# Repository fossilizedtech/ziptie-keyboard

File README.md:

# ziptie-keyboard
Everyone has their own preference when it comes to keyboards. This is my attempt to make my dream keyboard. There are a lot of ideas that will be implemented over time and I do not recommend using this as a foundation for any other project unless you don't value your time. I am not an electrical engineer, and I have no idea what I'm doing. I'm just throwing bits and pieces together, hoping that I don't end up burning my house to the ground in the process.

Now that you have been warned, if you want to build this board here is what you will need.

# Bill of Materials
Add materials here

# Building
Step by step instructions on how to get what you need to build and how to build

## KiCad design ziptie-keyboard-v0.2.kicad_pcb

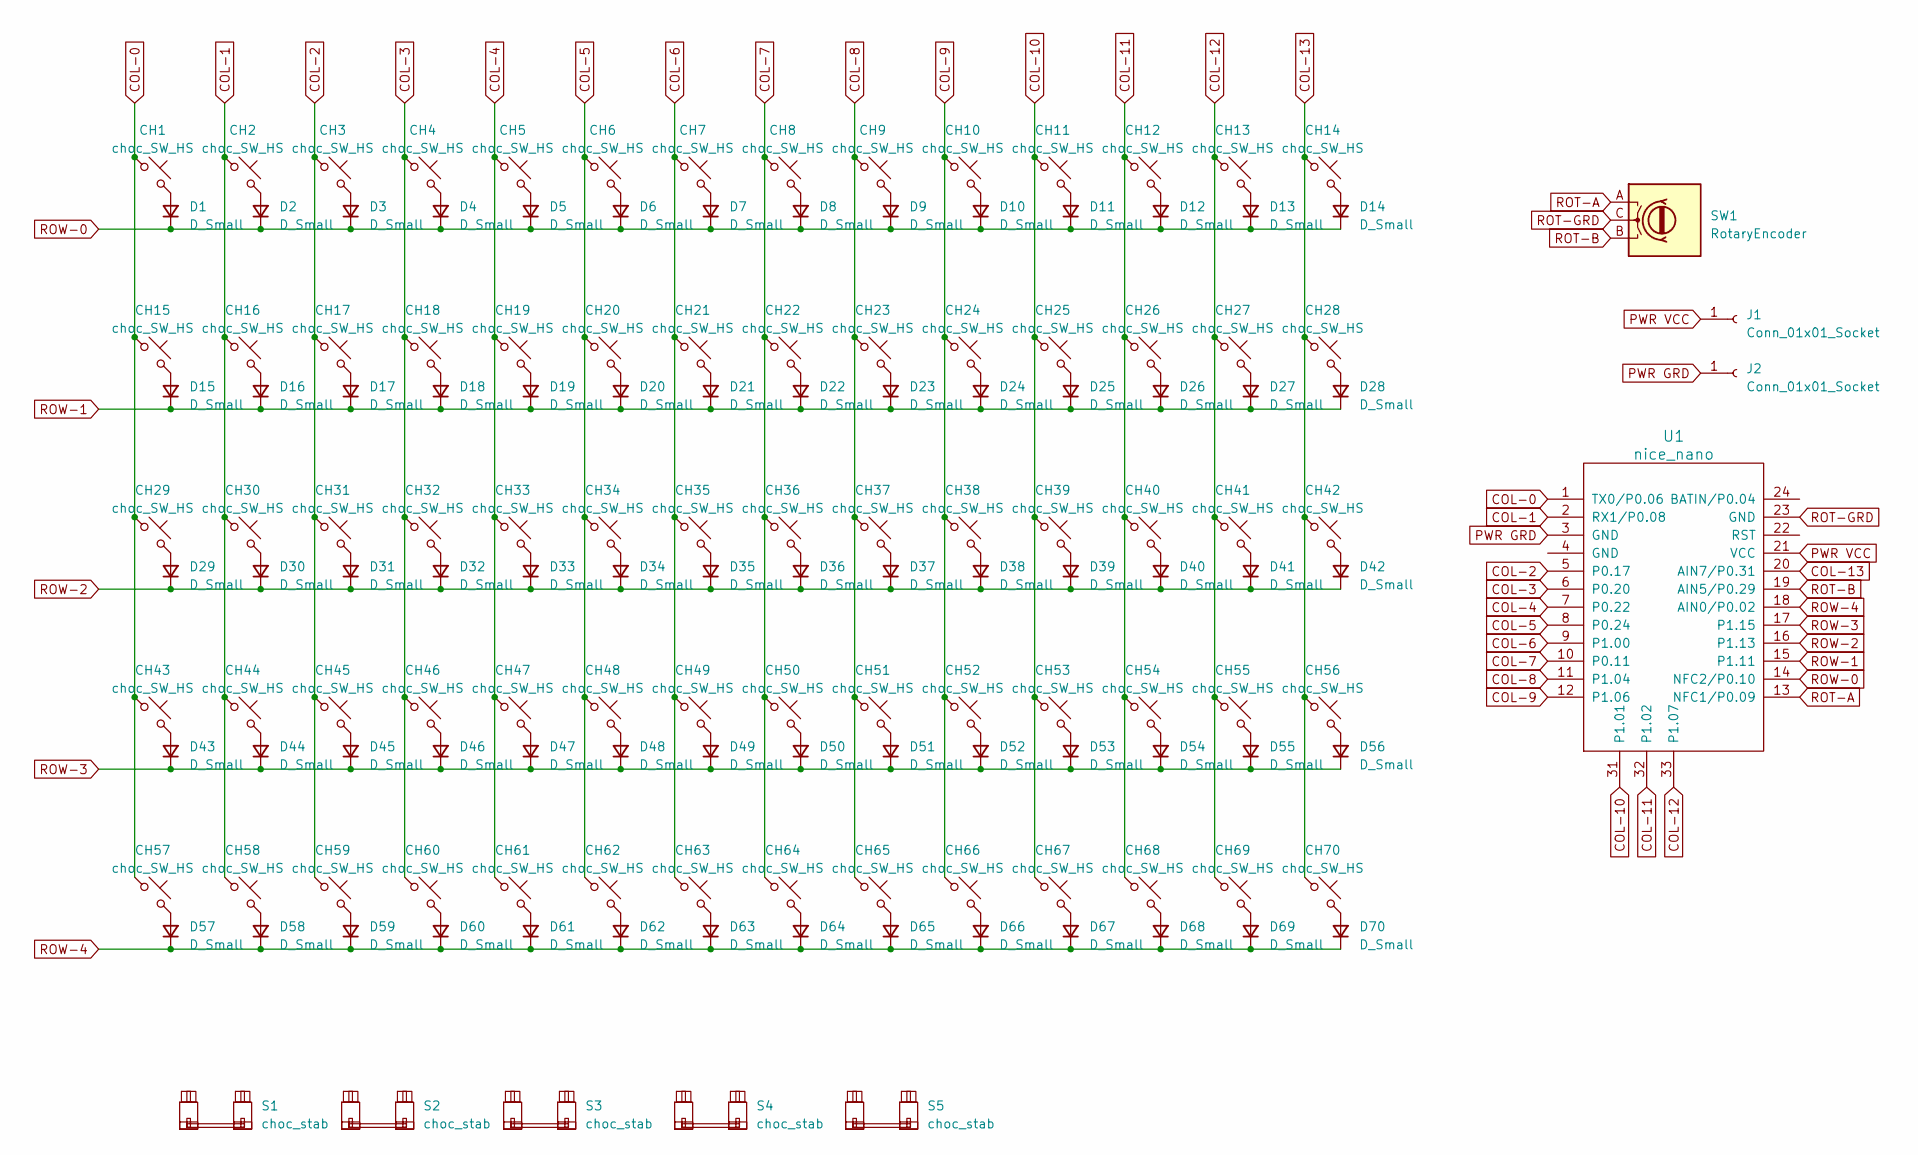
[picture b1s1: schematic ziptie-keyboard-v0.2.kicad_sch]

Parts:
CH1, CH2, CH3, CH4, CH5, CH6, CH7, CH8, CH9, CH10, CH11, CH12, CH13, CH14, CH16, CH17, CH18, CH19, CH20, CH21, CH22, CH23, CH24, CH25, CH26, CH27, CH30, CH31, CH32, CH33, CH34, CH35, CH36, CH37, CH38, CH39, CH40, CH41, CH42, CH43, CH44, CH45, CH46, CH47, CH48, CH49, CH50, CH51, CH52, CH53, CH55, CH56, CH60, CH61, CH62, CH63, CH64, CH65, CH67, CH68, CH69, CH70: choc_SW_HS; SW_choc_v1_HS_1u
CH15, CH28: choc_SW_HS; SW_choc_v1_HS_1.5u
CH29, CH54: choc_SW_HS; SW_choc_v1_HS_1.75u
CH57, CH58, CH59, CH66: choc_SW_HS; SW_choc_v1_HS_1.25u
D1, D2, D3, D4, D5, D6, D7, D8, D9, D10, D11, D12, D13, D14, D15, D16, D17, D18, D19, D20, D21, D22, D23, D24, D25, D26, D27, D28, D29, D30, D31, D32, D33, D34, D35, D36, D37, D38, D39, D40, D41, D42, D43, D44, D45, D46, D47, D48, D49, D50, D51, D52, D53, D54, D55, D56, D57, D58, D59, D60, D61, D62, D63, D64, D65, D66, D67, D68, D69, D70: D_Small; D_SOD-123
J1, J2: Conn_01x01_Socket; SolderWire-0.1sqmm_1x01_D0.4mm_OD1mm
S1, S2, S3, S4, S5: choc_stab; STAB_choc_2u
SW1: RotaryEncoder; RotaryEncoder_Alps_EC12E_Vertical_H20mm
U1: nice_nano

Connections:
COL-0: CH1.1, CH15.1, CH29.1, CH43.1, CH57.1, U1.1 (TX0/P0.06)
COL-1: CH2.1, CH16.1, CH30.1, CH44.1, CH58.1, U1.2 (RX1/P0.08)
COL-2: CH3.1, CH17.1, CH31.1, CH45.1, CH59.1, U1.5 (P0.17)
COL-3: CH4.1, CH18.1, CH32.1, CH46.1, CH60.1, U1.6 (P0.20)
COL-4: CH5.1, CH19.1, CH33.1, CH47.1, CH61.1, U1.7 (P0.22)
COL-5: CH6.1, CH20.1, CH34.1, CH48.1, CH62.1, U1.8 (P0.24)
COL-6: CH7.1, CH21.1, CH35.1, CH49.1, CH63.1, U1.9 (P1.00)
COL-7: CH8.1, CH22.1, CH36.1, CH50.1, CH64.1, U1.10 (P0.11)
COL-8: CH9.1, CH23.1, CH37.1, CH51.1, CH65.1, U1.11 (P1.04)
COL-9: CH10.1, CH24.1, CH38.1, CH52.1, CH66.1, U1.12 (P1.06)
COL-10: CH11.1, CH25.1, CH39.1, CH53.1, CH67.1, U1.31 (P1.01)
COL-11: CH12.1, CH26.1, CH40.1, CH54.1, CH68.1, U1.32 (P1.02)
COL-12: CH13.1, CH27.1, CH41.1, CH55.1, CH69.1, U1.33 (P1.07)
COL-13: CH14.1, CH28.1, CH42.1, CH56.1, CH70.1, U1.20 (AIN7/P0.31)
unnamed: CH1.2, D1.2 (A)
unnamed: CH2.2, D2.2 (A)
unnamed: CH3.2, D3.2 (A)
unnamed: CH4.2, D4.2 (A)
unnamed: CH5.2, D5.2 (A)
unnamed: CH6.2, D6.2 (A)
unnamed: CH7.2, D7.2 (A)
unnamed: CH8.2, D8.2 (A)
unnamed: CH9.2, D9.2 (A)
unnamed: CH10.2, D10.2 (A)
unnamed: CH11.2, D11.2 (A)
unnamed: CH12.2, D12.2 (A)
unnamed: CH13.2, D13.2 (A)
unnamed: CH14.2, D14.2 (A)
unnamed: CH15.2, D15.2 (A)
unnamed: CH16.2, D16.2 (A)
unnamed: CH17.2, D17.2 (A)
unnamed: CH18.2, D18.2 (A)
unnamed: CH19.2, D19.2 (A)
unnamed: CH20.2, D20.2 (A)
unnamed: CH21.2, D21.2 (A)
unnamed: CH22.2, D22.2 (A)
unnamed: CH23.2, D23.2 (A)
unnamed: CH24.2, D24.2 (A)
unnamed: CH25.2, D25.2 (A)
unnamed: CH26.2, D26.2 (A)
unnamed: CH27.2, D27.2 (A)
unnamed: CH28.2, D28.2 (A)
unnamed: CH29.2, D29.2 (A)
unnamed: CH30.2, D30.2 (A)
unnamed: CH31.2, D31.2 (A)
unnamed: CH32.2, D32.2 (A)
unnamed: CH33.2, D33.2 (A)
unnamed: CH34.2, D34.2 (A)
unnamed: CH35.2, D35.2 (A)
unnamed: CH36.2, D36.2 (A)
unnamed: CH37.2, D37.2 (A)
unnamed: CH38.2, D38.2 (A)
unnamed: CH39.2, D39.2 (A)
unnamed: CH40.2, D40.2 (A)
unnamed: CH41.2, D41.2 (A)
unnamed: CH42.2, D42.2 (A)
unnamed: CH43.2, D43.2 (A)
unnamed: CH44.2, D44.2 (A)
unnamed: CH45.2, D45.2 (A)
unnamed: CH46.2, D46.2 (A)
unnamed: CH47.2, D47.2 (A)
unnamed: CH48.2, D48.2 (A)
unnamed: CH49.2, D49.2 (A)
unnamed: CH50.2, D50.2 (A)
unnamed: CH51.2, D51.2 (A)
unnamed: CH52.2, D52.2 (A)
unnamed: CH53.2, D53.2 (A)
unnamed: CH54.2, D54.2 (A)
unnamed: CH55.2, D55.2 (A)
unnamed: CH56.2, D56.2 (A)
unnamed: CH57.2, D57.2 (A)
unnamed: CH58.2, D58.2 (A)
unnamed: CH59.2, D59.2 (A)
unnamed: CH60.2, D60.2 (A)
unnamed: CH61.2, D61.2 (A)
unnamed: CH62.2, D62.2 (A)
unnamed: CH63.2, D63.2 (A)
unnamed: CH64.2, D64.2 (A)
unnamed: CH65.2, D65.2 (A)
unnamed: CH66.2, D66.2 (A)
unnamed: CH67.2, D67.2 (A)
unnamed: CH68.2, D68.2 (A)
unnamed: CH69.2, D69.2 (A)
unnamed: CH70.2, D70.2 (A)
PWR GRD: J2.1, U1.3 (GND)
PWR VCC: J1.1, U1.21 (VCC)
ROT-A: SW1.A, U1.13 (NFC1/P0.09)
ROT-B: SW1.B, U1.19 (AIN5/P0.29)
ROT-GRD: SW1.C, U1.23 (GND)
ROW-0: D1.1 (K), D2.1 (K), D3.1 (K), D4.1 (K), D5.1 (K), D6.1 (K), D7.1 (K), D8.1 (K), D9.1 (K), D10.1 (K), D11.1 (K), D12.1 (K), D13.1 (K), D14.1 (K), U1.14 (NFC2/P0.10)
ROW-1: D15.1 (K), D16.1 (K), D17.1 (K), D18.1 (K), D19.1 (K), D20.1 (K), D21.1 (K), D22.1 (K), D23.1 (K), D24.1 (K), D25.1 (K), D26.1 (K), D27.1 (K), D28.1 (K), U1.15 (P1.11)
ROW-2: D29.1 (K), D30.1 (K), D31.1 (K), D32.1 (K), D33.1 (K), D34.1 (K), D35.1 (K), D36.1 (K), D37.1 (K), D38.1 (K), D39.1 (K), D40.1 (K), D41.1 (K), D42.1 (K), U1.16 (P1.13)
ROW-3: D43.1 (K), D44.1 (K), D45.1 (K), D46.1 (K), D47.1 (K), D48.1 (K), D49.1 (K), D50.1 (K), D51.1 (K), D52.1 (K), D53.1 (K), D54.1 (K), D55.1 (K), D56.1 (K), U1.17 (P1.15)
ROW-4: D57.1 (K), D58.1 (K), D59.1 (K), D60.1 (K), D61.1 (K), D62.1 (K), D63.1 (K), D64.1 (K), D65.1 (K), D66.1 (K), D67.1 (K), D68.1 (K), D69.1 (K), D70.1 (K), U1.18 (AIN0/P0.02)

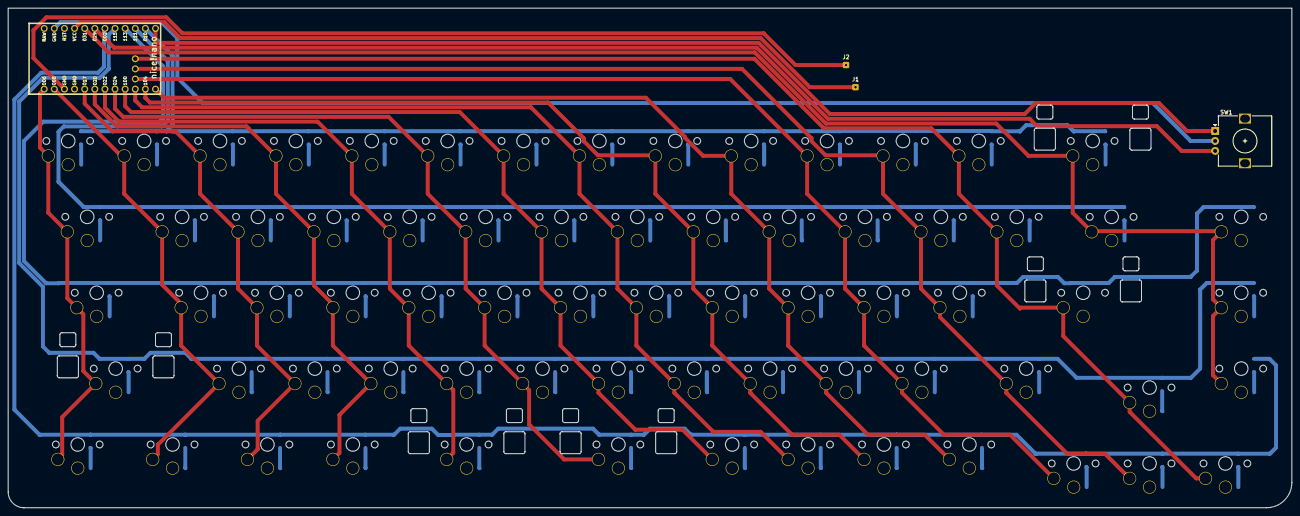
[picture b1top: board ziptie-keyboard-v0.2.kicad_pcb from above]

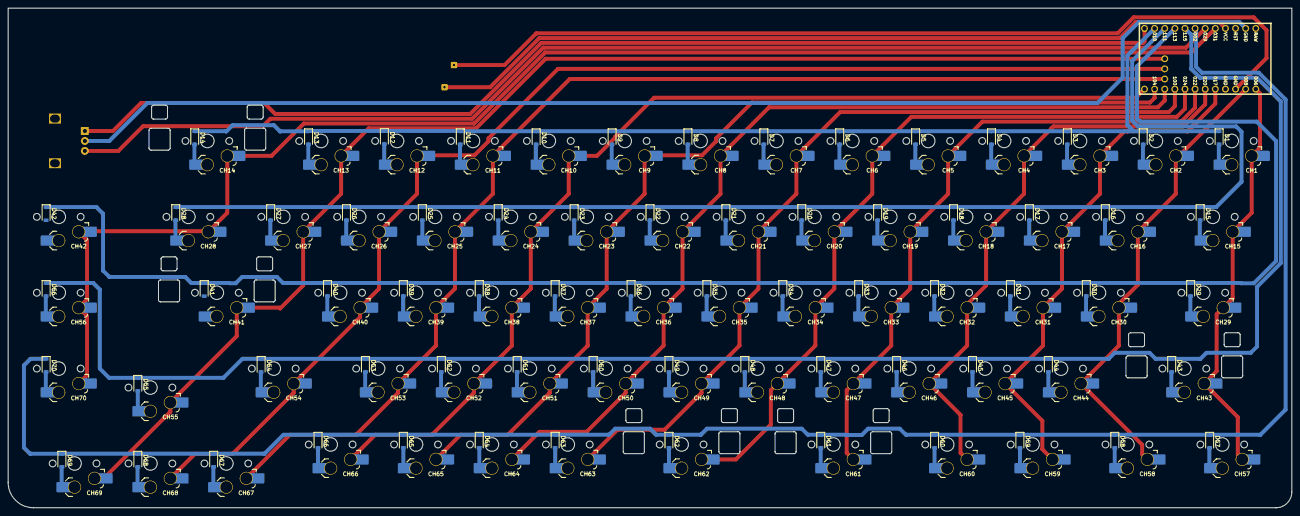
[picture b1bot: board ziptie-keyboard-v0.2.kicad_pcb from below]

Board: 2 copper layers, 322.3 x 125.4 mm, 149 parts (140 on the bottom side), 94 nets.

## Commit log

2023-05-03 Update readme
    put in warnings not to use this repo for anything serious
2023-05-03 Added png showing general keyboard layout
2023-05-03 Added Kicad files
2023-05-03 Removed autosave
2023-05-03 Updated traces to 1mm and traced matrix
2023-05-03 Added placeholders for BOM and steps to build
2023-05-04 Added traces and board cuts
2023-06-27 Reworked matrix, added pwr switch, btry and deco
2023-06-27 Added keyboard layout image
    Uploaded an updated image as the layout has changed
2023-06-28 Updated silk screen
